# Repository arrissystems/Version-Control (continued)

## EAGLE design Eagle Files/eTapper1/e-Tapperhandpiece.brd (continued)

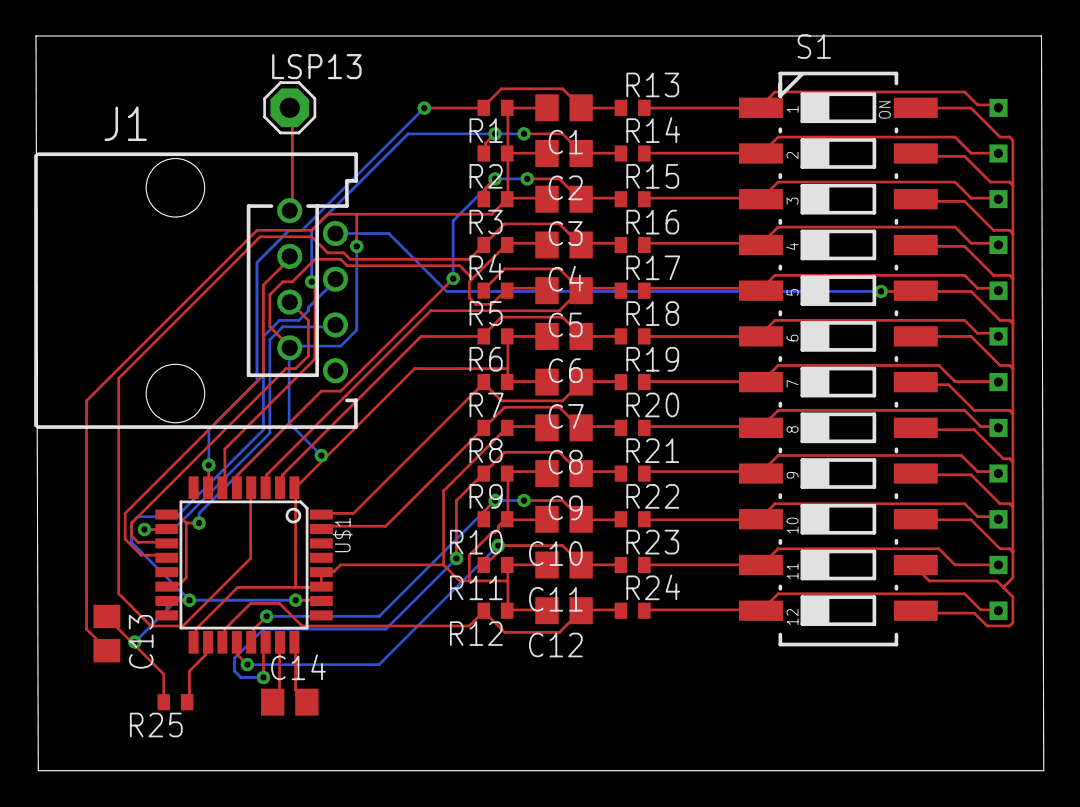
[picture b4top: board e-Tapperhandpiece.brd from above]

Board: 2 copper layers, 56.0 x 40.8 mm, 56 parts (0 on the bottom side), 34 nets.

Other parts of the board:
DRILEGEND: DRILEGEND

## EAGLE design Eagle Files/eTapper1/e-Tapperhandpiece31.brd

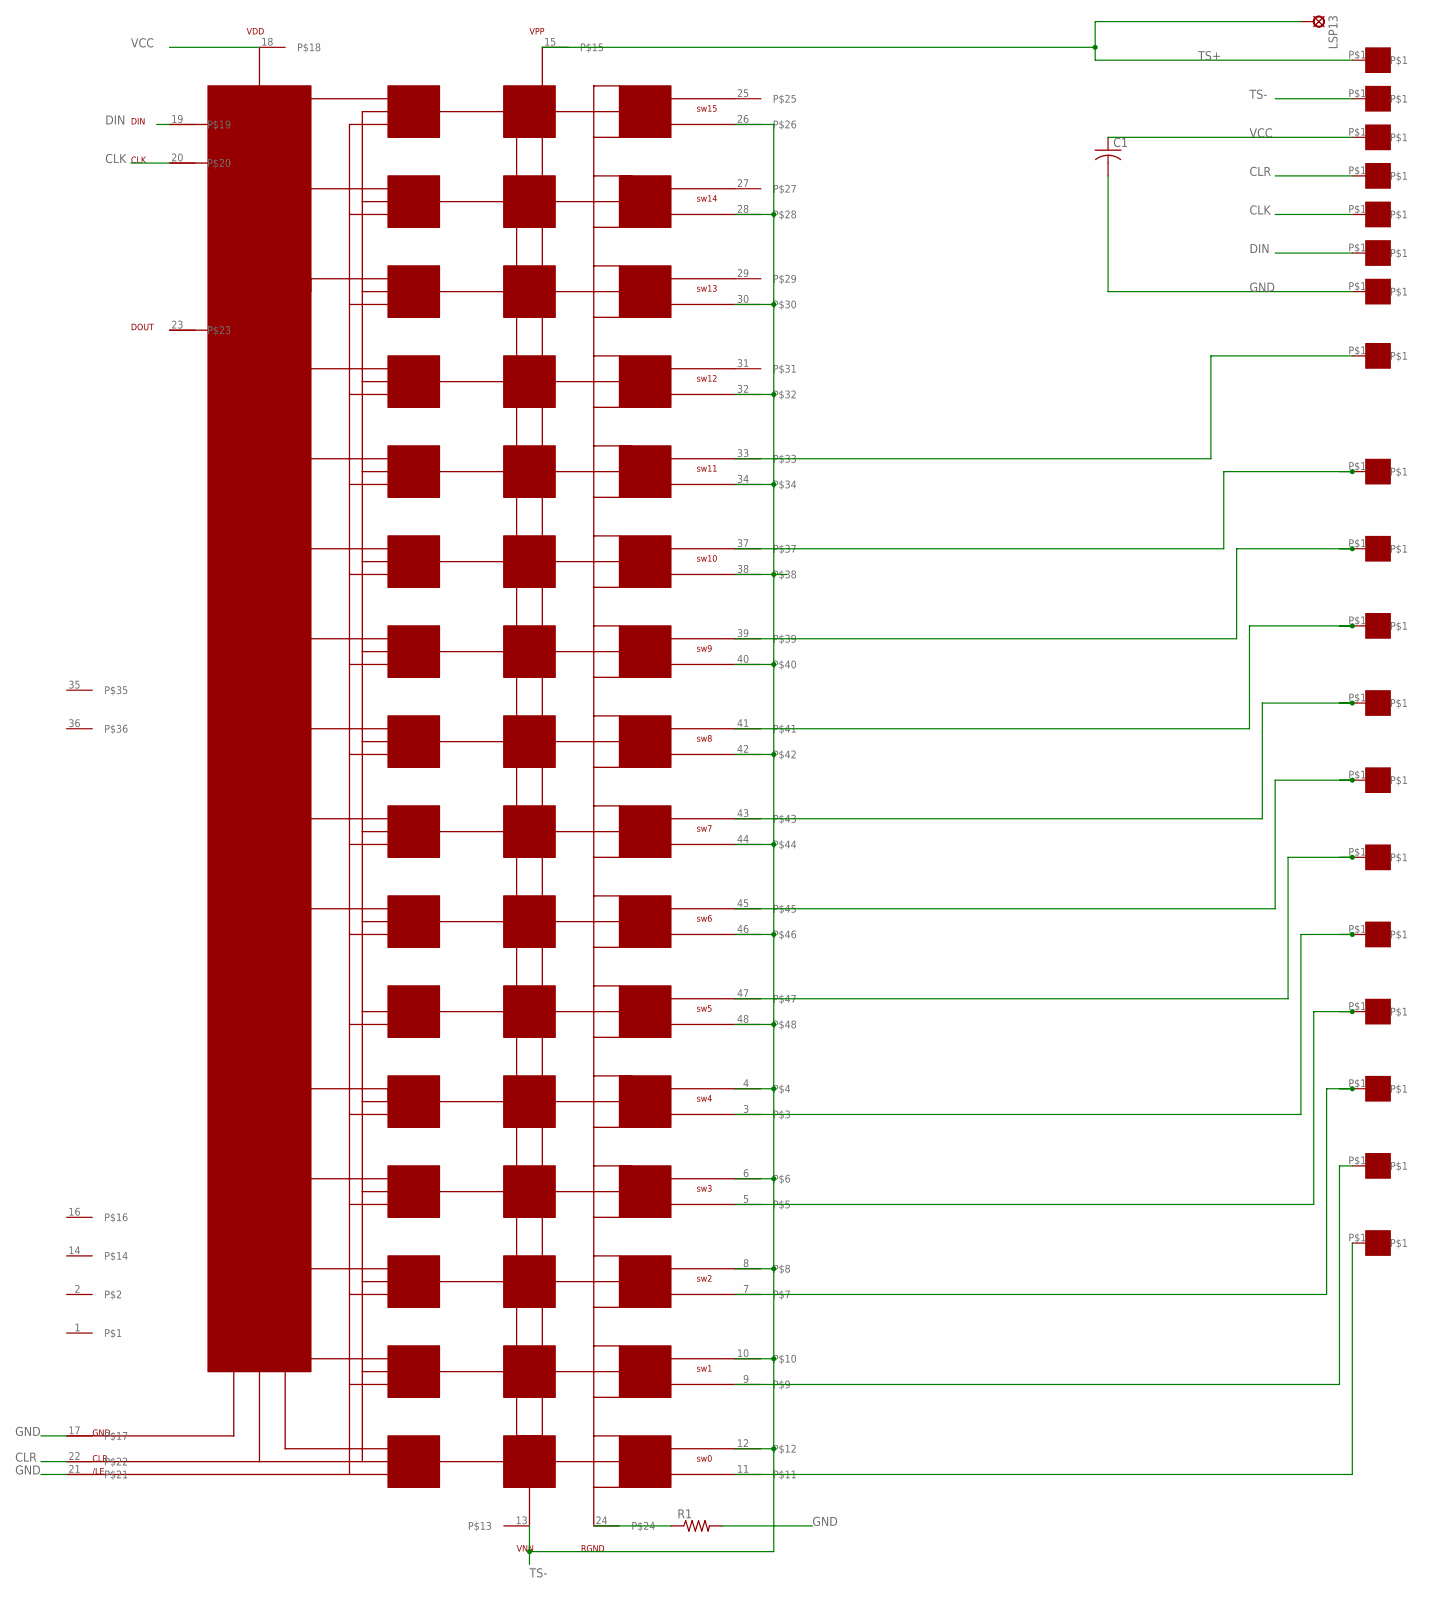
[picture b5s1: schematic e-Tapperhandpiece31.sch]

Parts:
C1: C-USC0805; C0805
LSP13: SE11
R1: R-US_R0805; R0805
TSP1, TSP2, TSP3, TSP4, TSP5, TSP6, TSP7, TSP8, TSP9, TSP10, TSP11, TSP12, TSP13, TSP14, TSP16, TSP17, TSP18, TSP19: ET1
U1: CPC7701; LQFP48
VCC: ET1

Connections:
CLK: TSP17.P$1, U1.20
CLR: TSP18.P$1, U1.22
DIN: TSP16.P$1, U1.19
GND: C1.2, R1.2, TSP19.P$1, U1.17, U1.21
unnamed: R1.1, U1.24
unnamed: TSP1.P$1, U1.33
unnamed: TSP2.P$1, U1.37
unnamed: TSP3.P$1, U1.39
unnamed: TSP4.P$1, U1.41
unnamed: TSP5.P$1, U1.43
unnamed: TSP6.P$1, U1.45
unnamed: TSP7.P$1, U1.47
unnamed: TSP8.P$1, U1.3
unnamed: TSP9.P$1, U1.5
unnamed: TSP10.P$1, U1.7
unnamed: TSP11.P$1, U1.9
unnamed: TSP12.P$1, U1.11
TS+: LSP13.MP, TSP13.P$1, U1.15
TS-: TSP14.P$1, U1.4, U1.6, U1.8, U1.10, U1.12, U1.13, U1.26, U1.28, U1.30, U1.32, U1.34, U1.38, U1.40, U1.42, U1.44, U1.46, U1.48
VCC: C1.1, U1.18, VCC.P$1

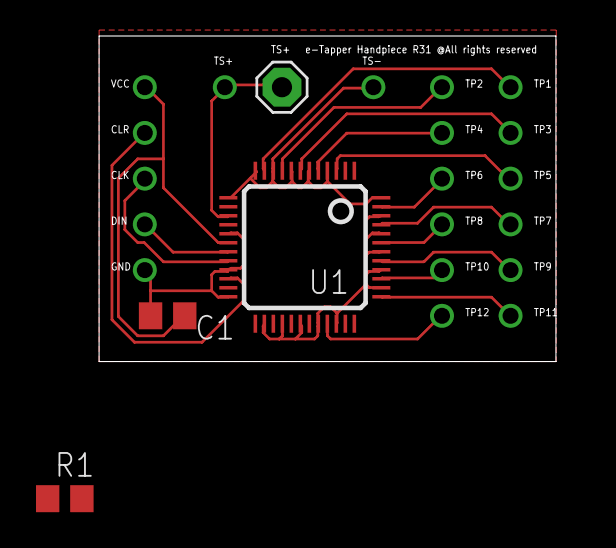
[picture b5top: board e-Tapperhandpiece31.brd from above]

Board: 2 copper layers, 25.4 x 18.1 mm, 23 parts (0 on the bottom side), 20 nets.

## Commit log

2018-04-19 eTapperMain Main.c version 1 4/18/2018
2018-04-19 Include header files.
2018-04-19 eTapperMain Main.c version 1 4/19/2018
2018-06-15 Version 5
    Version 5
2018-06-23 Fixed some arays Version 5.1
    Fixed leftbar[11] to leftbar[12] and rightbar[11] to rightbar[12] add needsetvoltage for recall to set voltages, change selchan to start with 1 to 12.
    keep voltage set when pulsexfmr
    keep Port 1 interrupts turn off until switch is ready for debounce
2018-06-23 Version 5.2
    Clean up comments
2018-07-23 Version 6 finer bars and stepper motor control
    Added finer bars and stepper motor control
